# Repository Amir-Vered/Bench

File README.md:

# Bench

<p align="center">
  🎥 <a href="https://youtu.be/uZiKh8IRC8s">Video</a> &nbsp;•&nbsp; 🌐 <a href="https://amirvered.com/project/bench">Writeup</a>
</p>

<p align="center">
  <a href="#project-goals">Project Goals</a> •
  <a href="#system-overview">System Overview</a> •
  <a href="#diagrams">Diagrams</a> •
  <a href="#hardware">Hardware</a> •
  <a href="#software">Software</a> •
  <a href="#license">License</a>
</p>

---

*Bench... and it's not made out of wood?*

Here's the pitch:

TL;DR wires are annoying, let's put Bench in the middle of the Arduino workflow.

I love Arduino, it's perfect for prototyping your projects before making your PCBs. 
But, idk about you, the most annoying thing to me is the fact that the board is tied to my laptop.
And it's not a graceful connection, no, these wires are some of the most stale twisted things you've ever used, especially the uni lab ones.
This gets even worse when you're using a desktop computer.
But what if we put a device in the middle?

Enter: Bench.

Bench is a wifi upload dock for Arduino (built primarily for the Uno R3 because it's the one I use most).
Compile your sketch, run a command, and boom, it uploads to your device somewhere else.
No more wire, Arduino dev becomes a little less life-draining.

This is a simple little project, but it's open source, and I hope you find some use out of it.
Feel free to leave issues, fork, or really do whatever you want with it.

## Project Goals

My goals for this project were to:
- Improve the Arduino dev experience
- Develop my hardware, firmware, and software design skills
- Document a project from beginning to end

## System Overview

Let's get into the details.

At a high level:

1. The laptop compiles an Arduino sketch into a `.hex` file.
2. The CLI sends the `.hex` file to Bench over Wi-Fi.
3. The ESP32-S3 on Bench receives the upload request.
4. Bench opens a USB host serial connection to the Arduino Uno R3.
5. Bench triggers the Uno bootloader window.
6. Bench uploads the program to the ATmega328P flash memory.

Bench does not compile Arduino code on-board; compilation happens on the laptop.

## Diagrams

### Labeled Board

### System Block Diagram

### Power Path

### Upload/Data Flow

## Repository Structure

```text
bench/
├── hardware/
│   ├── kicad/
│   └── exports/
├── software/
│   ├── mock/
│   │   └── bench-mock-server/
│   ├── cli/
│   │   └── bench-upload/
│   └── firmware/
│       └── bench-fw/
├── media/
│   ├── diagrams/
│   ├── renders/
│   └── screenshots/
├── LICENSE-SOFTWARE
├── LICENSE-HARDWARE
└── README.md
```

## Hardware

Bench is built around the ESP32-S3-WROOM-1.

Major hardware blocks include:

- USB-C 5V input
- Input protection using a PTC fuse and TVS diode
- 3.3V buck regulator for the ESP32-S3
- ESP32-S3-WROOM-1 Wi-Fi microcontroller
- USB-A host output for the Arduino Uno R3
- TPS2553 current-limited USB power switch
- USB data ESD protection
- Status LEDs for power, Wi-Fi, target, upload, and fault states
- Reset and boot/config buttons

## Software

Bench includes three software components:

```text
software/
├── mock/
│   └── bench-mock-server/
├── cli/
│   └── bench-upload/
└── firmware/
    └── bench-fw/
```

### Mock Server

The mock server simulates a Bench device on a local computer. It is used to test the CLI without Bench hardware.

```powershell
cd software\mock\bench-mock-server
python -m venv .venv
.venv\Scripts\Activate.ps1
python -m pip install --upgrade pip
python -m pip install -e .
bench-mock --port 8080
```

Test the mock server:

```text
http://127.0.0.1:8080/api/v1/status
```

### CLI

The Bench Upload CLI runs on the laptop, and can communicate with the firmware or mock server.

```powershell
cd software\cli\bench-upload
python -m venv .venv
.venv\Scripts\Activate.ps1
python -m pip install --upgrade pip
python -m pip install -e .
```

#### *Here's how to use the commands, demoed on the mock server...*

Check Bench status:

```powershell
bench status --device http://localhost:8080
```

Upload a precompiled Intel HEX file:

```powershell
bench upload --hex path\to\sketch.ino.hex --device http://localhost:8080
```

Upload without target reset:

```powershell
bench upload --hex path\to\sketch.ino.hex --no-reset --device http://localhost:8080
```

Upload without verify:

```powershell
bench upload --hex path\to\sketch.ino.hex --no-verify --device http://localhost:8080
```

Compile an Arduino sketch with Arduino CLI, then upload:

```powershell
bench upload path\to\Blink --fqbn arduino:avr:uno --device http://localhost:8080
```

### Firmware

The firmware is an ESP-IDF project for the ESP32-S3.

```powershell
cd software\firmware\bench-fw
idf.py set-target esp32s3
idf.py build
```

Wi-Fi settings are configured locally with:

```powershell
idf.py menuconfig
```

Then open:

```text
Bench Configuration
```

and set:

```text
Wi-Fi SSID
Wi-Fi password
```

## Firmware Features

Current firmware includes:

- Wi-Fi station startup
- HTTP API server
    - `GET /api/v1/status`
    - `POST /api/v1/target/power`
    - `POST /api/v1/target/reset`
    - `GET /api/v1/logs`
    - `POST /api/v1/upload`
    - `GET /api/v1/upload/{job_id}`
- ESP32-S3 USB host CDC
- Arduino Uno R3 Optiboot/STK500 upload path (🤞😩)
- GPIO control for TPS2553 target power
- GPIO control for status LEDs

The firmware builds successfully for ESP32-S3, but I haven't had the chance to test it on hardware, so be careful.

## API Overview

Bench firmware and the mock server expose the same main HTTP API shape.

```text
GET  /api/v1/status
POST /api/v1/upload
GET  /api/v1/upload/{job_id}
POST /api/v1/target/power
POST /api/v1/target/reset
GET  /api/v1/logs
```

Primary upload states:

```text
idle
receiving
opening_target
bootloader_sync
uploading
verifying
success
failed
fault
```

Primary error codes:

```text
INVALID_HEX
NO_TARGET
POWER_FAULT
USB_OPEN_FAILED
BOOTLOADER_TIMEOUT
UPLOAD_FAILED
VERIFY_FAILED
POWER_DISABLED
```

## Current Status

Bench Rev A is a complete prototype, but I haven't had the chance to fabricate it yet.

I'm confident in my hardware and software design, but the firmware, well, let's just say it was my first time programming an ESP32-S3... 😅

Something else pretty cool about this project is the documentation. I've created a video, a post on my website, this repo, and so much more, with full diagrams and explanations.
It's been part of my goal to build more in public, and this is one of the projects I'm most proud of so far. 
My chess board (ICB, 1/26-6/26) was awesome, but its docs were scattered. 
Bench is hopefully the start of a more cohesive online doc cycle, stay tuned for more.

In terms of future Bench additions, if there is a Rev B, expect:
- more in-depth CLI
- hardware redesign, maybe
- 3D printable exterior / mounts
- and more

## License

* **Software:** Licensed under the **[MIT License](LICENSE-SOFTWARE)**.
* **Hardware:** Schematics and PCB layouts are licensed under the **[CERN-OHL-P-2.0](LICENSE-HARDWARE)** (CERN Open Hardware Licence Version 2 - Permissive).
* **Media & Documentation:** Renders, diagrams, and written assets are **© 2026 Amir Vered** unless otherwise stated. All rights reserved.

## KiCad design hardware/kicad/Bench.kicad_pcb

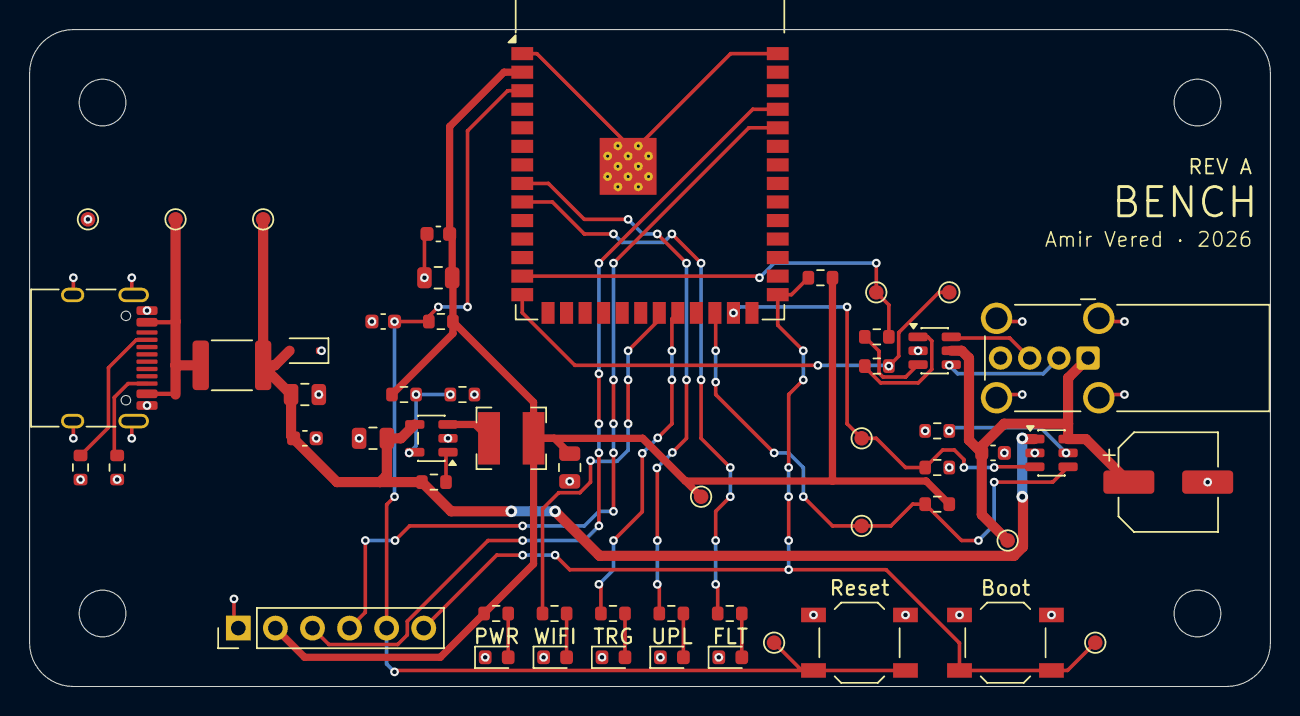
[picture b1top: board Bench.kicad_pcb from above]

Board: 2 copper layers, 85.0 x 45.0 mm, 54 parts (0 on the bottom side), 32 nets.

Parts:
Boot: Boot; SW_SPST_TL3342
C1, C3, C4, C6: 10uF; C_0805_2012Metric
C2, C5, C7, C9: 0.1uF; C_0603_1608Metric
C8: 120uF; CP_Elec_6.3x5.8
D1: TSD05; D_SOD-323
F1: 1A hold; Fuse_1812_4532Metric
FLT: LED_FAULT; LED_0603_1608Metric
J1: USB_C; USB_C_Receptacle_HRO_TYPE-C-31-M-12
J2: J_ESP_PROG; PinHeader_1x06_P2.54mm_Vertical
J3: USB_A; USB_A_Wuerth_614004134726_Horizontal
L1: 2.2uH; L_Bourns-SRN4018
PWR: LED_PWR; LED_0603_1608Metric
R1, R2: 5.1k; R_0603_1608Metric
R3: 453k; R_0603_1608Metric
R4, R5, R9: 100k; R_0603_1608Metric
R6, R7, R10: 10k; R_0603_1608Metric
R8: 59k; R_0603_1608Metric
R11, R12, R13, R14, R15: 1k; R_0603_1608Metric
R16, R17: 22R; R_0603_1608Metric
Reset: Reset; SW_SPST_TL3342
TP1: TP_5V_PROTECTED; TestPoint_Pad_D1.0mm
TP2: TP_3V3; TestPoint_Pad_D1.0mm
TP3: TP_VBUS_IN; TestPoint_Pad_D1.0mm
TP4: TP_USB_A_VBUS; TestPoint_Pad_D1.0mm
TP5: TP_GND; TestPoint_Pad_D1.0mm
TP6: TP_USB_D-; TestPoint_Pad_D1.0mm
TP7: TP_USB_D+; TestPoint_Pad_D1.0mm
TP8: TP_TPS_FAULT; TestPoint_Pad_D1.0mm
TP9: TP_TPS_EN; TestPoint_Pad_D1.0mm
TP10: TP_ESP_BOOT; TestPoint_Pad_D1.0mm
TP11: TP_ESP_EN; TestPoint_Pad_D1.0mm
TRG: LED_TARGET; LED_0603_1608Metric
U1: TLV62569DBVR; SOT-23-5
U2: ESP32-S3-WROOM-1-N8R8; ESP32-S3-WROOM-1
U3: USBLC6-2SC6; SOT-23-6
U4: TPS2553DBV; SOT-23-6
UPL: LED_UPLOAD; LED_0603_1608Metric
WIFI: LED_WIFI; LED_0603_1608Metric

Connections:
/+3V3: C4.1, C6.2, C7.2, J2.2, L1.2, R3.1, R6.2, R7.2, R10.2, R11.1, TP2.1 (1_1), U2.2 (3V3)
/+5V_PROTECTED: C1.2, C2.1, C3.2, D1.2 (A), F1.1, R4.2, TP1.1 (1_1), U1.4 (VIN), U4.1 (IN)
/ESP_BOOT: Boot.2, J2.6, R7.1, TP10.1 (1_1), U2.27 (IO0)
/ESP_EN: C5.1, J2.5, R6.1, Reset.2, TP11.1 (1_1), U2.3 (EN)
/ESP_RXD0: J2.4, U2.36 (RXD0)
/ESP_TXD0: J2.3, U2.37 (TXD0)
/ILIM: R8.2, U4.5 (ILIM)
/LED_FAULT: R15.1, U2.9 (IO16)
/LED_TARGET: R13.1, U2.22 (IO14)
/LED_UPLOAD: R14.1, U2.8 (IO15)
/LED_WIFI: R12.1, U2.21 (IO13)
/TPS_EN: R9.1, TP9.1 (1_1), U2.25 (IO48), U4.3 (EN)
/TPS_FAULT: R10.1, TP8.1 (1_1), U2.24 (IO47), U4.4 (FAULT)
/USB_A_VBUS: C8.1, C9.1, J3.1 (VBUS), TP4.1 (1_1), U3.5 (VBUS), U4.6 (OUT)
/VBUS_IN: F1.2, J1.A4 (VBUS), J1.A9 (VBUS), J1.B4 (VBUS), J1.B9 (VBUS), TP3.1 (1_1)
GND: Boot.1, C1.1, C2.2, C3.1, C4.2, C5.2, C6.1, C7.1, C8.2, C9.2, D1.1 (K), FLT.1 (K), J1.A1 (GND), J1.A12 (GND), J1.B1 (GND), J1.B12 (GND), J1.SH (SHIELD), J2.1, J3.4 (GND), J3.SH (Shield), PWR.1 (K), R1.2, R2.1, R5.2, R8.1, R9.2, Reset.1, TP5.1 (1_1), TRG.1 (K), U1.2 (GND), U2.1 (GND), U2.40 (GND), U2.41 (GND), U3.2 (GND), U4.2 (GND), UPL.1 (K), WIFI.1 (K)
unnamed: PWR.2 (A), R11.2
unnamed: R12.2, WIFI.2 (A)
unnamed: R13.2, TRG.2 (A)
unnamed: R14.2, UPL.2 (A)
unnamed: FLT.2 (A), R15.2
unnamed: J1.A5 (CC1), R1.1
unnamed: J1.B5 (CC2), R2.2
unnamed: J3.3 (D+), U3.6 (I/O1)
unnamed: J3.2 (D-), U3.4 (I/O2)
unnamed: R16.2, U3.3 (I/O2)
unnamed: R17.2, U3.1 (I/O1)
unnamed: R4.1, U1.1 (EN)
unnamed: R3.2, R5.1, U1.5 (FB)
unnamed: L1.1, U1.3 (SW)
unnamed: R17.1, TP7.1 (1_1), U2.14 (USB_D+)
unnamed: R16.1, TP6.1 (1_1), U2.13 (USB_D-)

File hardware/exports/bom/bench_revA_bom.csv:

"Reference","Qty","Value","DNP","Exclude from BOM","Exclude from Board","Footprint","Datasheet"
"C1,C3,C4,C6","4","10uF","","","","Capacitor_SMD:C_0805_2012Metric",""
"C2,C5,C7,C9","4","0.1uF","","","","Capacitor_SMD:C_0603_1608Metric",""
"C8","1","120uF","","","","Capacitor_SMD:CP_Elec_6.3x5.8",""
"D1","1","TSD05","","","","Diode_SMD:D_SOD-323",""
"D2","1","LED_PWR","","","","LED_SMD:LED_0603_1608Metric",""
"D3","1","LED_WIFI","","","","LED_SMD:LED_0603_1608Metric",""
"D4","1","LED_TARGET","","","","LED_SMD:LED_0603_1608Metric",""
"D5","1","LED_UPLOAD","","","","LED_SMD:LED_0603_1608Metric",""
"D6","1","LED_FAULT","","","","LED_SMD:LED_0603_1608Metric",""
"F1","1","1A hold","","","","Fuse:Fuse_1812_4532Metric",""
"J1","1","USB_C_Receptacle_USB2.0_16P","","","","Connector_USB:USB_C_Receptacle_HRO_TYPE-C-31-M-12","https://www.usb.org/sites/default/files/documents/usb_type-c.zip"
"J2","1","J_ESP_PROG","","","","Connector_PinHeader_2.54mm:PinHeader_1x06_P2.54mm_Vertical",""
"J3","1","USB_A","","","","Connector_USB:USB_A_Wuerth_614004134726_Horizontal",""
"L1","1","2.2uH","","","","Inductor_SMD:L_Bourns-SRN4018",""
"R1,R2","2","5.1k","","","","Resistor_SMD:R_0603_1608Metric",""
"R3","1","453k","","","","Resistor_SMD:R_0603_1608Metric",""
"R4,R5,R9","3","100k","","","","Resistor_SMD:R_0603_1608Metric",""
"R6,R7,R10","3","10k","","","","Resistor_SMD:R_0603_1608Metric",""
"R8","1","59k","","","","Resistor_SMD:R_0603_1608Metric",""
"R11,R12,R13,R14,R15","5","1k","","","","Resistor_SMD:R_0603_1608Metric",""
"R16,R17","2","22R","","","","Resistor_SMD:R_0603_1608Metric",""
"SW1","1","Reset","","","","Button_Switch_SMD:SW_SPST_TL3342",""
"SW2","1","Boot","","","","Button_Switch_SMD:SW_SPST_TL3342",""
"TP1","1","TP_5V_PROTECTED","","","","TestPoint:TestPoint_Pad_D1.0mm",""
"TP2","1","TP_3V3","","","","TestPoint:TestPoint_Pad_D1.0mm",""
"TP3","1","TP_VBUS_IN","","","","TestPoint:TestPoint_Pad_D1.0mm",""
"TP4","1","TP_USB_A_VBUS","","","","TestPoint:TestPoint_Pad_D1.0mm",""
"TP5","1","TP_GND","","","","TestPoint:TestPoint_Pad_D1.0mm",""
"TP6","1","TP_USB_D-","","","","TestPoint:TestPoint_Pad_D1.0mm",""
"TP7","1","TP_USB_D+","","","","TestPoint:TestPoint_Pad_D1.0mm",""
"TP8","1","TP_TPS_FAULT","","","","TestPoint:TestPoint_Pad_D1.0mm",""
"TP9","1","TP_TPS_EN","","","","TestPoint:TestPoint_Pad_D1.0mm",""
"TP10","1","TP_ESP_BOOT","","","","TestPoint:TestPoint_Pad_D1.0mm",""
"TP11","1","TP_ESP_EN","","","","TestPoint:TestPoint_Pad_D1.0mm",""
"U1","1","TLV62569DBVR","","","","Package_TO_SOT_SMD:SOT-23-5","http://www.ti.com/lit/ds/symlink/tlv62569.pdf"
"U2","1","ESP32-S3-WROOM-1-N8R8","","","","RF_Module:ESP32-S3-WROOM-1","https://www.espressif.com/sites/default/files/documentation/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"
"U3","1","USBLC6-2SC6","","","","Package_TO_SOT_SMD:SOT-23-6","https://www.st.com/resource/en/datasheet/usblc6-2.pdf"
"U4","1","TPS2553DBV","","","","Package_TO_SOT_SMD:SOT-23-6",""

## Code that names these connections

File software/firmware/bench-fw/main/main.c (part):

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#define STK_READ_PAGE 0x74
#define STK_LEAVE     0x51

#define GPIO_LED_WIFI     GPIO_NUM_13
#define GPIO_LED_TARGET   GPIO_NUM_14
#define GPIO_LED_UPLOAD   GPIO_NUM_15
#define GPIO_LED_FAULT    GPIO_NUM_16

#define GPIO_TPS_FAULT    GPIO_NUM_47
#define GPIO_TPS_EN       GPIO_NUM_48

#define LED_ON            1
#define LED_OFF           0
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}

static void bench_gpio_set_leds(bool wifi, bool target, bool upload, bool fault) {
    gpio_set_level(GPIO_LED_WIFI, wifi ? LED_ON : LED_OFF);
    gpio_set_level(GPIO_LED_TARGET, target ? LED_ON : LED_OFF);
    gpio_set_level(GPIO_LED_UPLOAD, upload ? LED_ON : LED_OFF);
    gpio_set_level(GPIO_LED_FAULT, fault ? LED_ON : LED_OFF);
}

static void bench_gpio_set_target_power(bool enabled) {
    gpio_set_level(GPIO_TPS_EN, enabled ? TPS_EN_ON : TPS_EN_OFF);
    target_power_enabled = enabled;
}

static bool bench_gpio_read_power_fault(void) {
    target_power_fault = gpio_get_level(GPIO_TPS_FAULT) == TPS_FAULT_ACTIVE;
    return target_power_fault;
}

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static esp_err_t bench_gpio_init(void) {
    gpio_config_t output_config = {
        .pin_bit_mask =
            (1ULL << GPIO_LED_WIFI) |
            (1ULL << GPIO_LED_TARGET) |
            (1ULL << GPIO_LED_UPLOAD) |
            (1ULL << GPIO_LED_FAULT) |
            (1ULL << GPIO_TPS_EN),
        .mode = GPIO_MODE_OUTPUT,
        .pull_up_en = GPIO_PULLUP_DISABLE,
        .pull_down_en = GPIO_PULLDOWN_DISABLE,
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    ESP_ERROR_CHECK(gpio_config(&output_config));

    gpio_config_t input_config = {
        .pin_bit_mask = (1ULL << GPIO_TPS_FAULT),
        .mode = GPIO_MODE_INPUT,
        .pull_up_en = GPIO_PULLUP_ENABLE,
        .pull_down_en = GPIO_PULLDOWN_DISABLE,
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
